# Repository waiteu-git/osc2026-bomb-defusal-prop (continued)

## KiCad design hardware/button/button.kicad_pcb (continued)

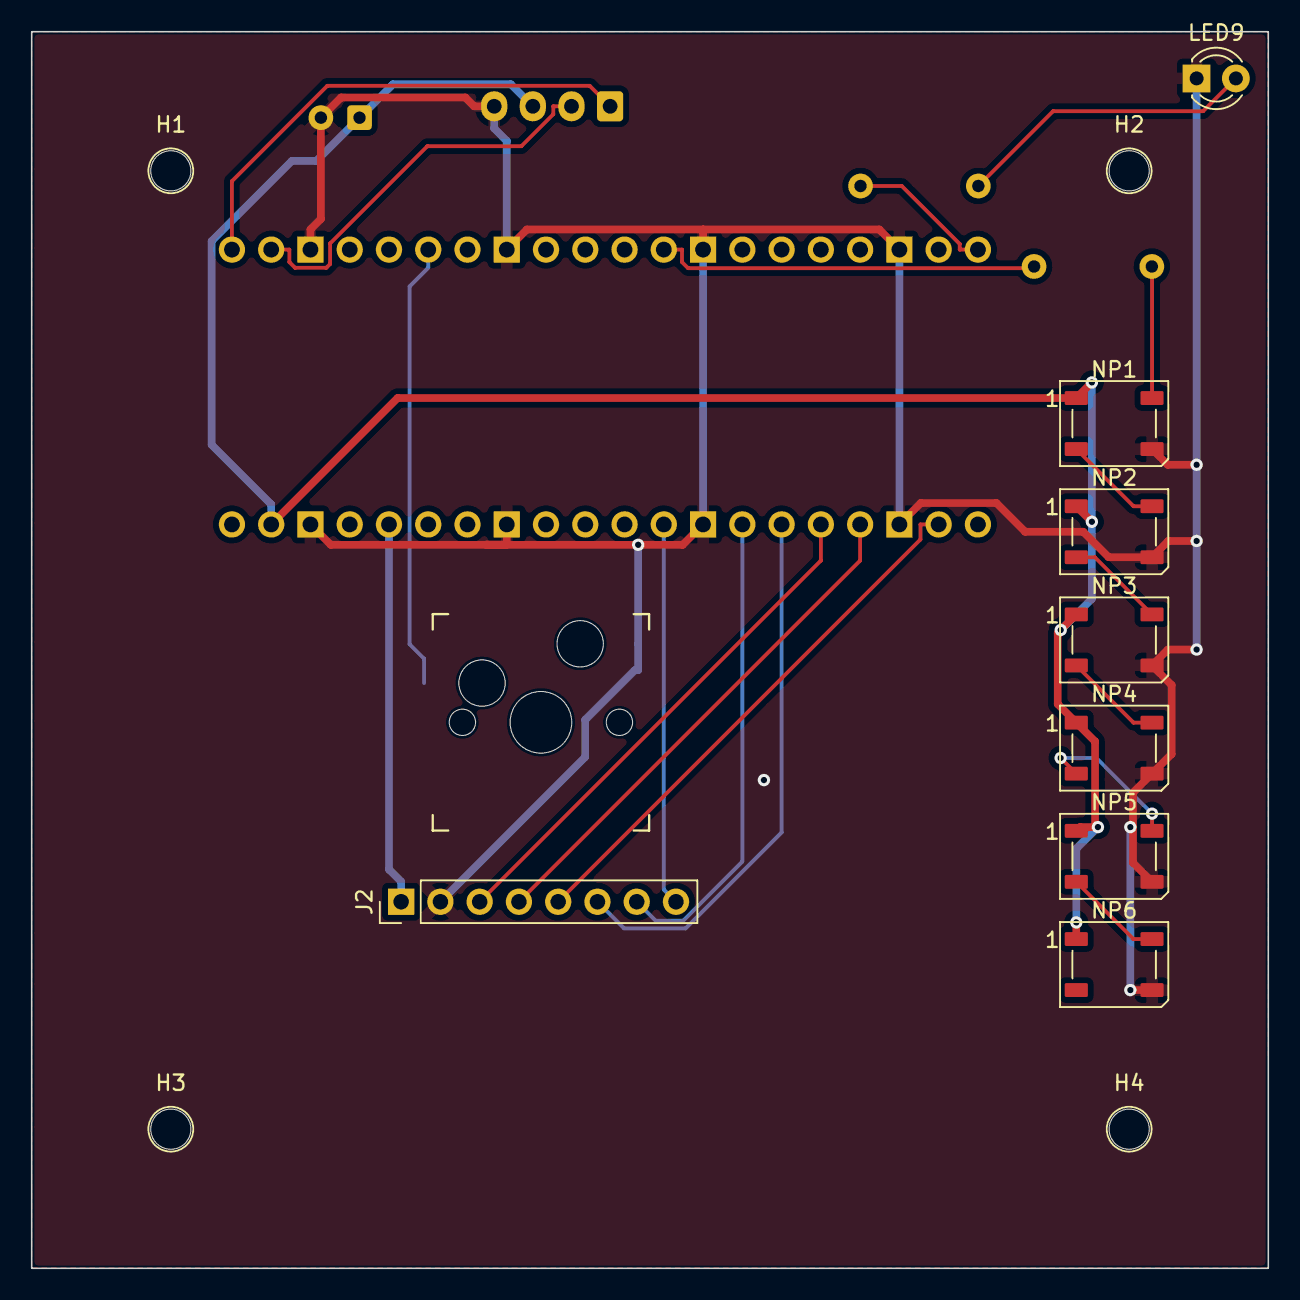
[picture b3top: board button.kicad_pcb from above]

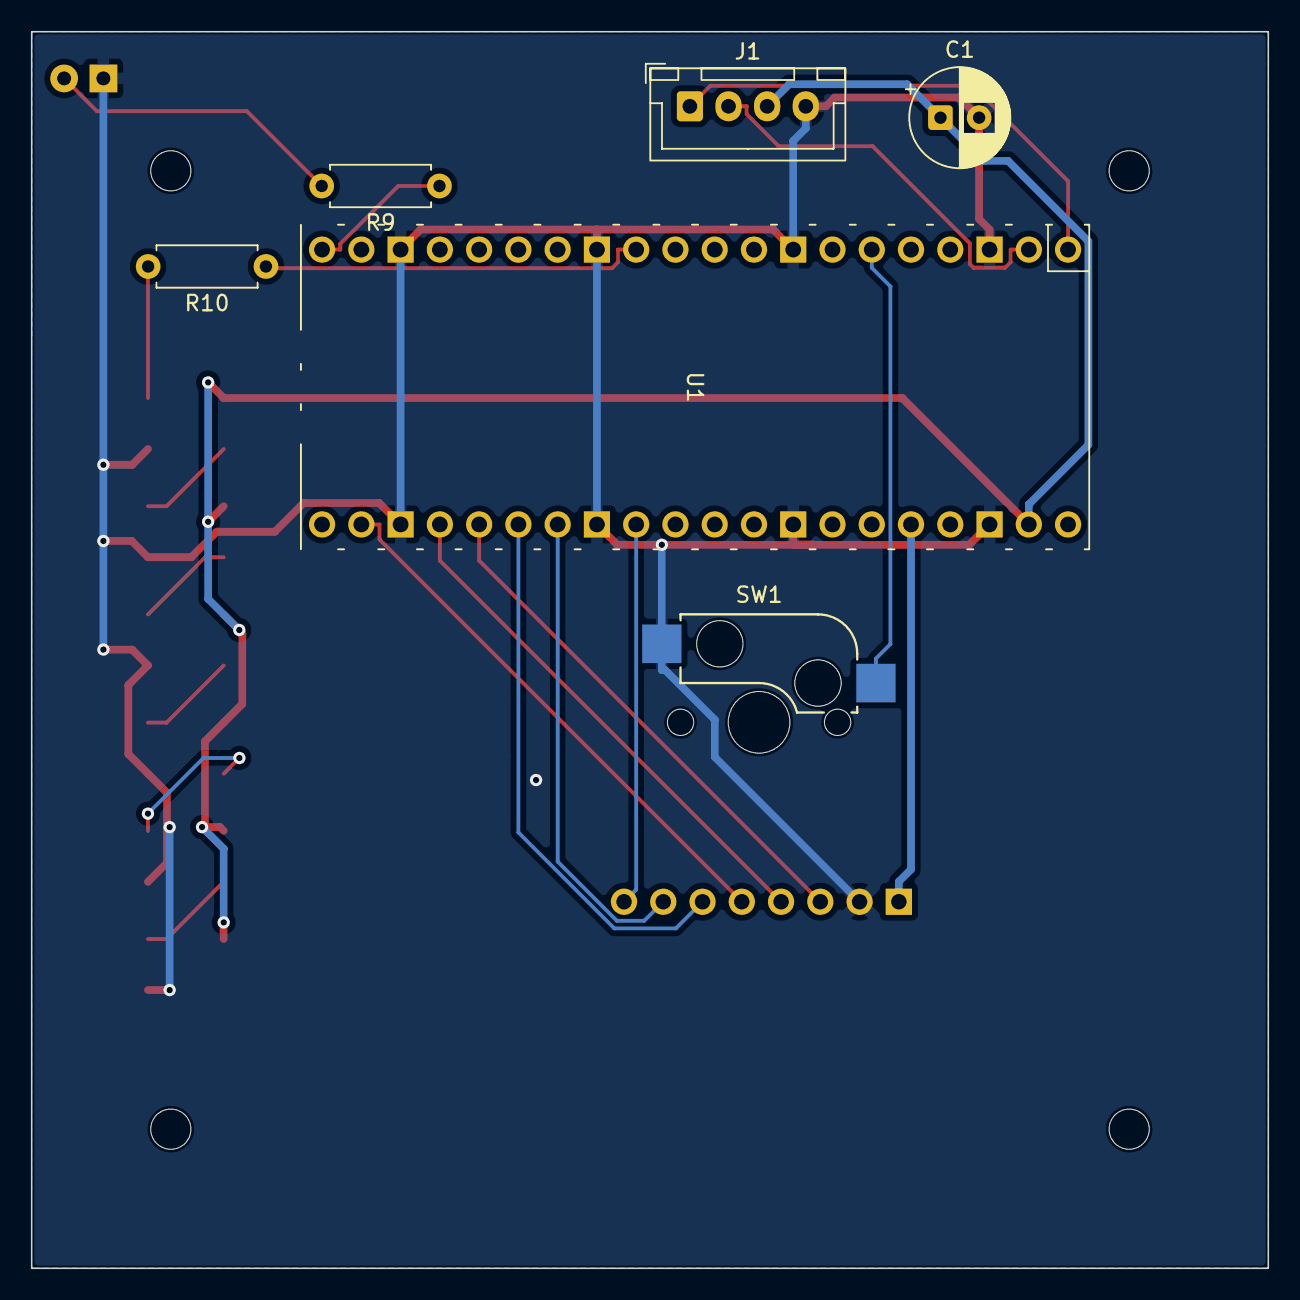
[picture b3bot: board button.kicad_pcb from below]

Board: 2 copper layers, 80.0 x 80.0 mm, 18 parts (5 on the bottom side), 21 nets.

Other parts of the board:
H1, H2, H3, H4: M2.6 hole (dia 2.6mm); MountingHole_2.6mm

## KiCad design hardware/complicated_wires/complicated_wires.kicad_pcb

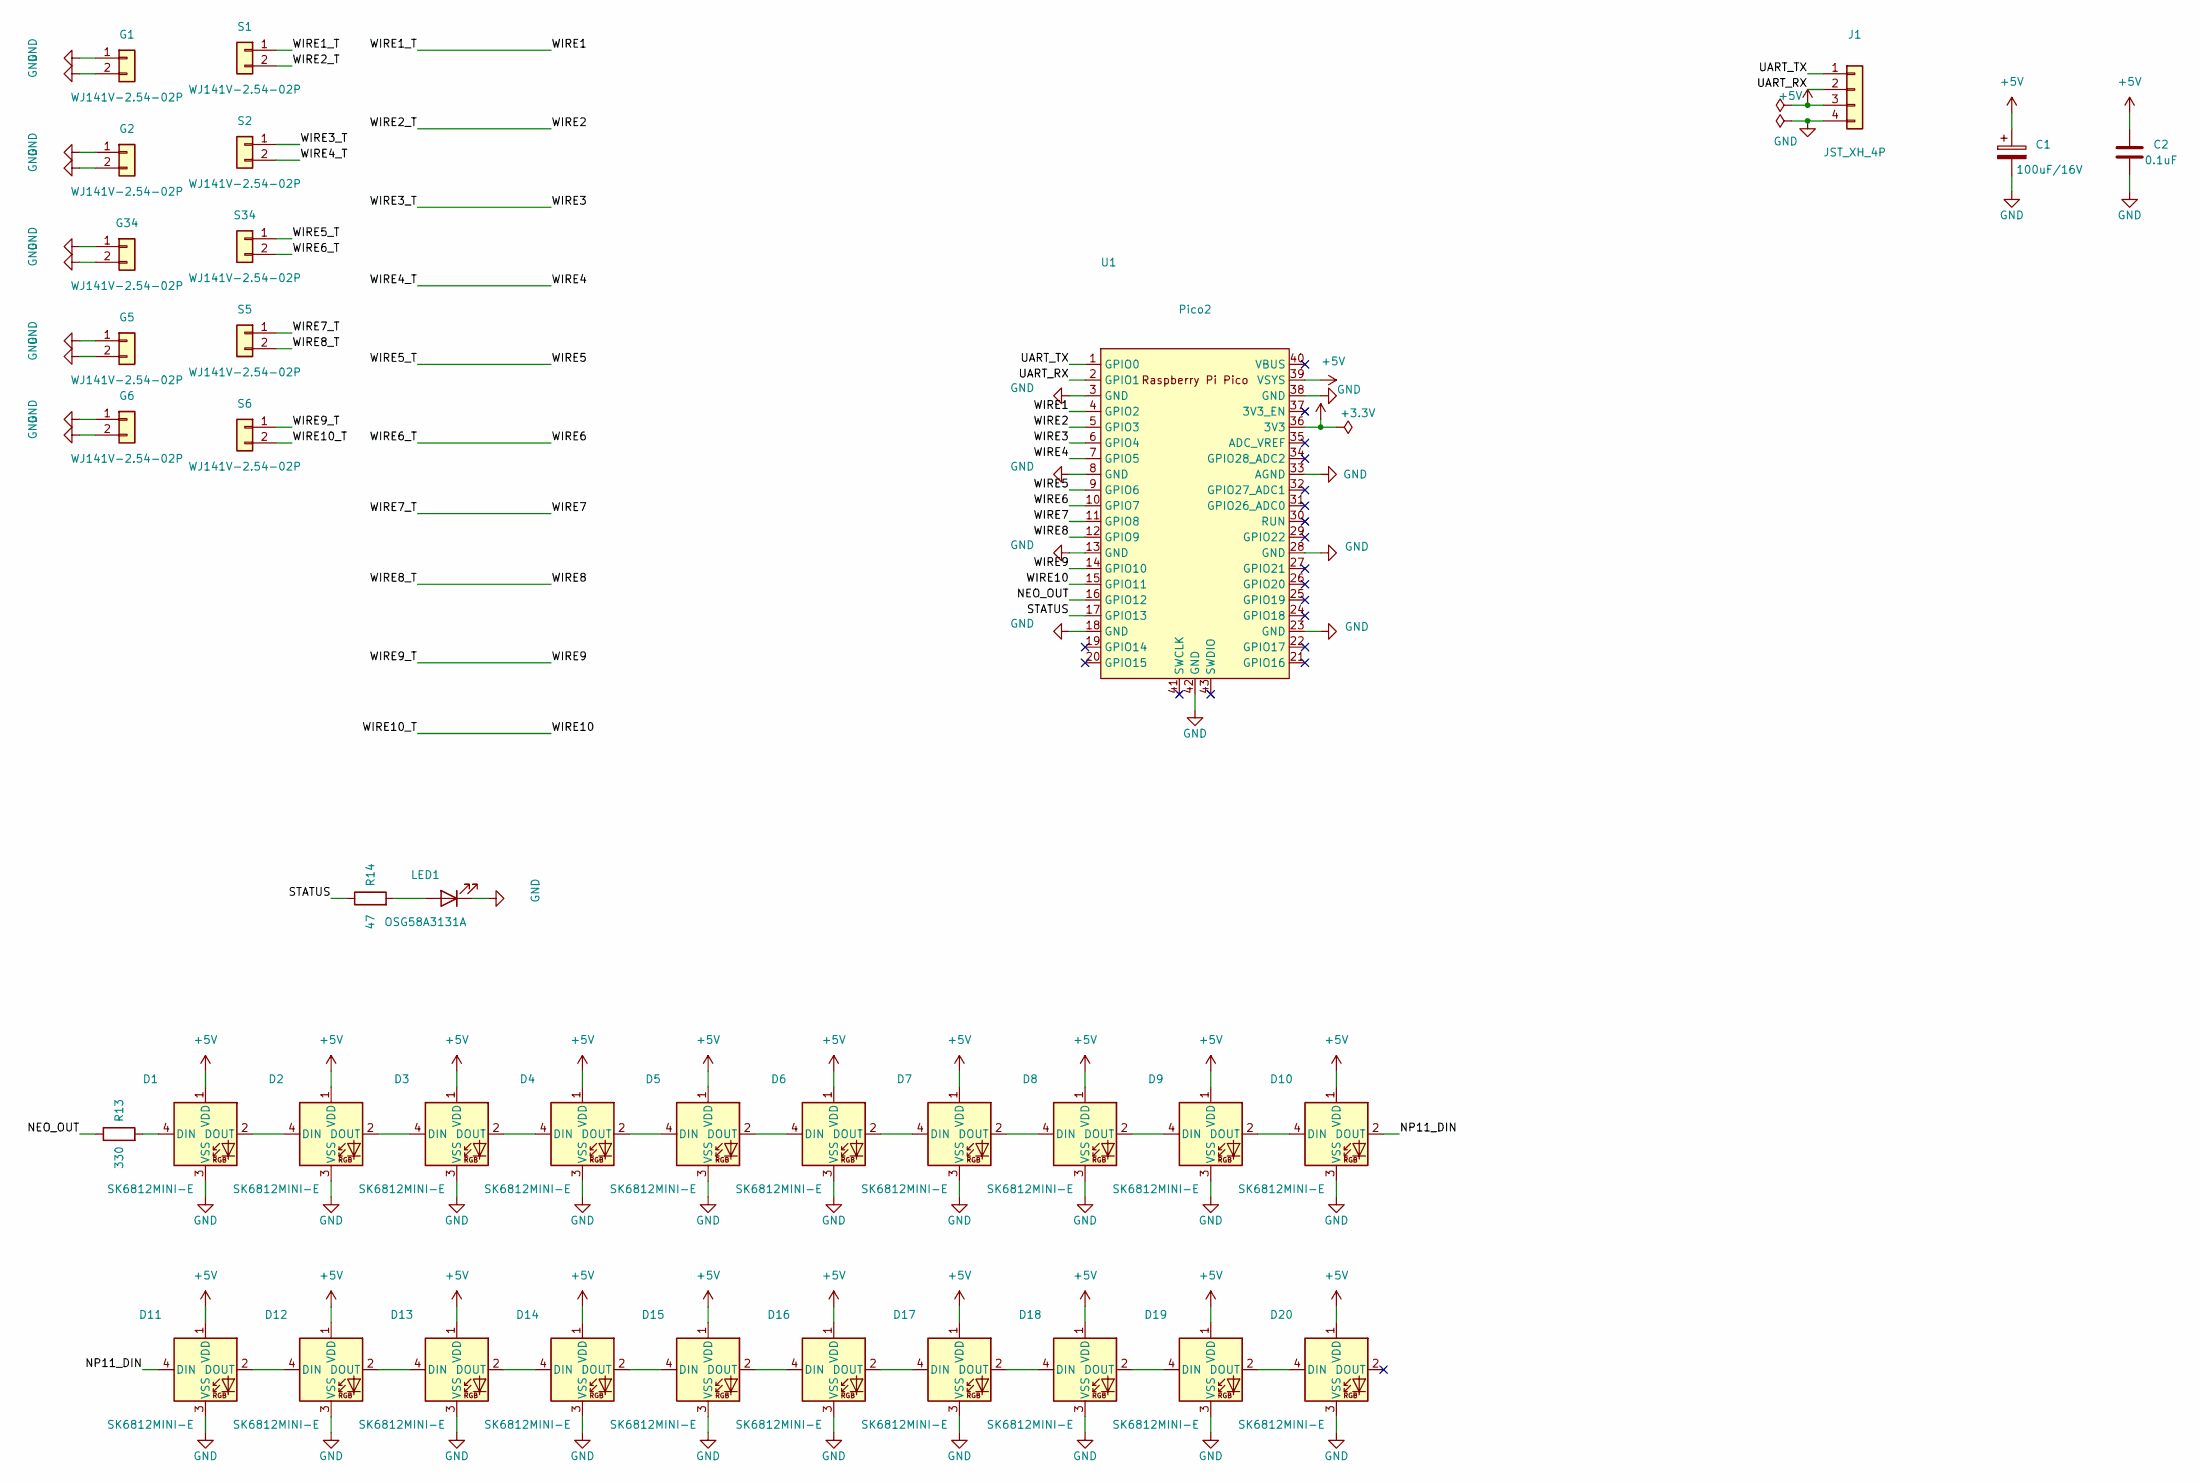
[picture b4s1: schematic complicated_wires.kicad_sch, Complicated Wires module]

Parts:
C1: 100uF/16V; CP_Radial_D6.3mm_P2.50mm
C2: 0.1uF; C_Disc_D5.0mm_W2.5mm_P5.00mm
D1, D2, D3, D4, D5, D6, D7, D8, D9, D10, D11, D12, D13, D14, D15, D16, D17, D18, D19, D20: SK6812MINI-E; LED_SK6812MINI-E_3.2x2.8mm_P1.5mm_ReverseMount
G1, G2, G5, G6, G34: WJ141V-2.54-02P; TerminalBlock_Phoenix_MKDS-1,5-2-5.08_1x02_P5.08mm_Horizont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
J1: JST_XH_4P; JST_XH_B4B-XH-A_1x04_P2.50mm_Vertical
LED1: OSG58A3131A; LED_D5.0mm
R13: 330; R_Axial_DIN0207_L6.3mm_D2.5mm_P10.16mm_Horizontal
R14: 47; R_Axial_DIN0207_L6.3mm_D2.5mm_P10.16mm_Horizontal
S1, S2, S5, S6, S34: WJ141V-2.54-02P; TerminalBlock_Phoenix_MKDS-1,5-2-5.08_1x02_P5.08mm_Horizont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
U1: Pico2; RPi_Pico_SMD_TH

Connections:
+3.3V: U1.36 (3V3)
+5V: C1.1, C2.1, D1.1 (VDD), D2.1 (VDD), D3.1 (VDD), D4.1 (VDD), D5.1 (VDD), D6.1 (VDD), D7.1 (VDD), D8.1 (VDD), D9.1 (VDD), D10.1 (VDD), D11.1 (VDD), D12.1 (VDD), D13.1 (VDD), D14.1 (VDD), D15.1 (VDD), D16.1 (VDD), D17.1 (VDD), D18.1 (VDD), D19.1 (VDD), D20.1 (VDD), J1.3, U1.39 (VSYS)
/NEO_OUT: R13.1, U1.16 (GPIO12)
/NP11_DIN: D10.2 (DOUT), D11.4 (DIN)
/STATUS: R14.1, U1.17 (GPIO13)
/UART_RX: J1.2, U1.2 (GPIO1)
/UART_TX: J1.1, U1.1 (GPIO0)
/WIRE1: S1.1, U1.4 (GPIO2)
/WIRE2: S1.2, U1.5 (GPIO3)
/WIRE3: S2.1, U1.6 (GPIO4)
/WIRE4: S2.2, U1.7 (GPIO5)
/WIRE5: S34.1, U1.9 (GPIO6)
/WIRE6: S34.2, U1.10 (GPIO7)
/WIRE7: S5.1, U1.11 (GPIO8)
/WIRE8: S5.2, U1.12 (GPIO9)
/WIRE9: S6.1, U1.14 (GPIO10)
/WIRE10: S6.2, U1.15 (GPIO11)
GND: C1.2, C2.2, D1.3 (VSS), D2.3 (VSS), D3.3 (VSS), D4.3 (VSS), D5.3 (VSS), D6.3 (VSS), D7.3 (VSS), D8.3 (VSS), D9.3 (VSS), D10.3 (VSS), D11.3 (VSS), D12.3 (VSS), D13.3 (VSS), D14.3 (VSS), D15.3 (VSS), D16.3 (VSS), D17.3 (VSS), D18.3 (VSS), D19.3 (VSS), D20.3 (VSS), G1.1, G1.2, G2.1, G2.2, G5.1, G5.2, G6.1, G6.2, G34.1, G34.2, J1.4, LED1.1 (K), U1.3 (GND), U1.8 (GND), U1.13 (GND), U1.18 (GND), U1.23 (GND), U1.28 (GND), U1.33 (AGND), U1.38 (GND), U1.42 (GND)
unnamed: D1.4 (DIN), R13.2
unnamed: D1.2 (DOUT), D2.4 (DIN)
unnamed: D2.2 (DOUT), D3.4 (DIN)
unnamed: D3.2 (DOUT), D4.4 (DIN)
unnamed: D4.2 (DOUT), D5.4 (DIN)
unnamed: D5.2 (DOUT), D6.4 (DIN)
unnamed: D6.2 (DOUT), D7.4 (DIN)
unnamed: D7.2 (DOUT), D8.4 (DIN)
unnamed: D8.2 (DOUT), D9.4 (DIN)
unnamed: D9.2 (DOUT), D10.4 (DIN)
unnamed: D11.2 (DOUT), D12.4 (DIN)
unnamed: D12.2 (DOUT), D13.4 (DIN)
unnamed: D13.2 (DOUT), D14.4 (DIN)
unnamed: D14.2 (DOUT), D15.4 (DIN)
unnamed: D15.2 (DOUT), D16.4 (DIN)
unnamed: D16.2 (DOUT), D17.4 (DIN)
unnamed: D17.2 (DOUT), D18.4 (DIN)
unnamed: D18.2 (DOUT), D19.4 (DIN)
unnamed: D19.2 (DOUT), D20.4 (DIN)
unnamed: LED1.2 (A), R14.2

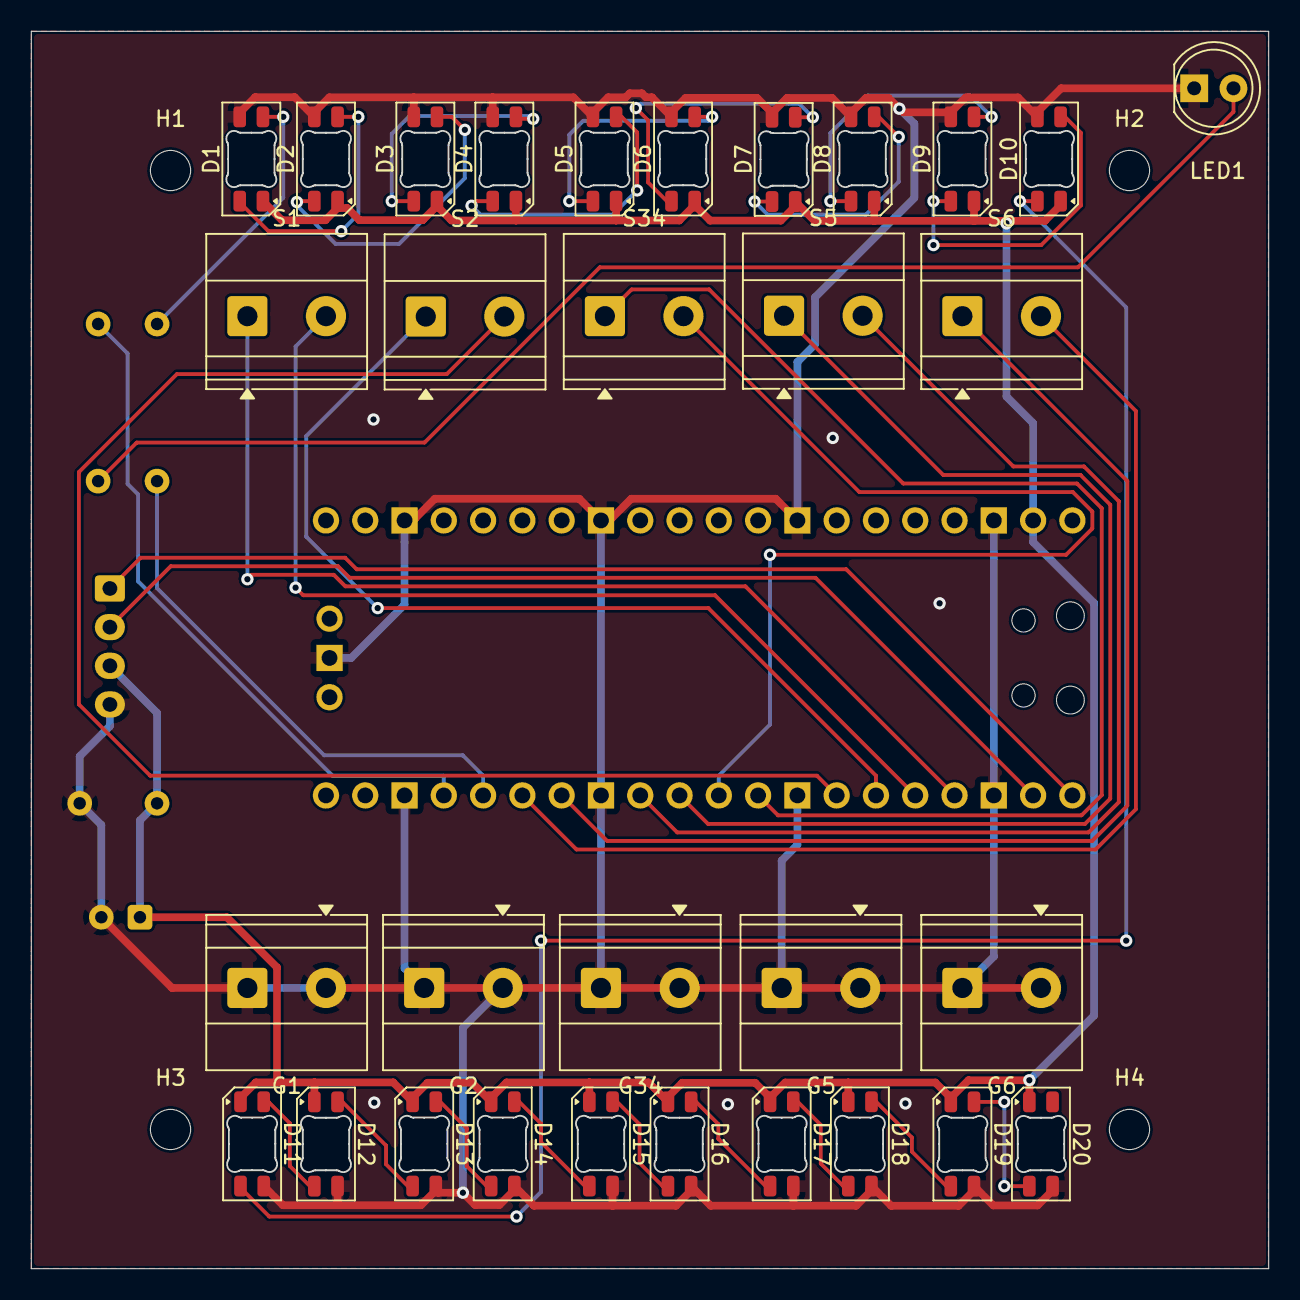
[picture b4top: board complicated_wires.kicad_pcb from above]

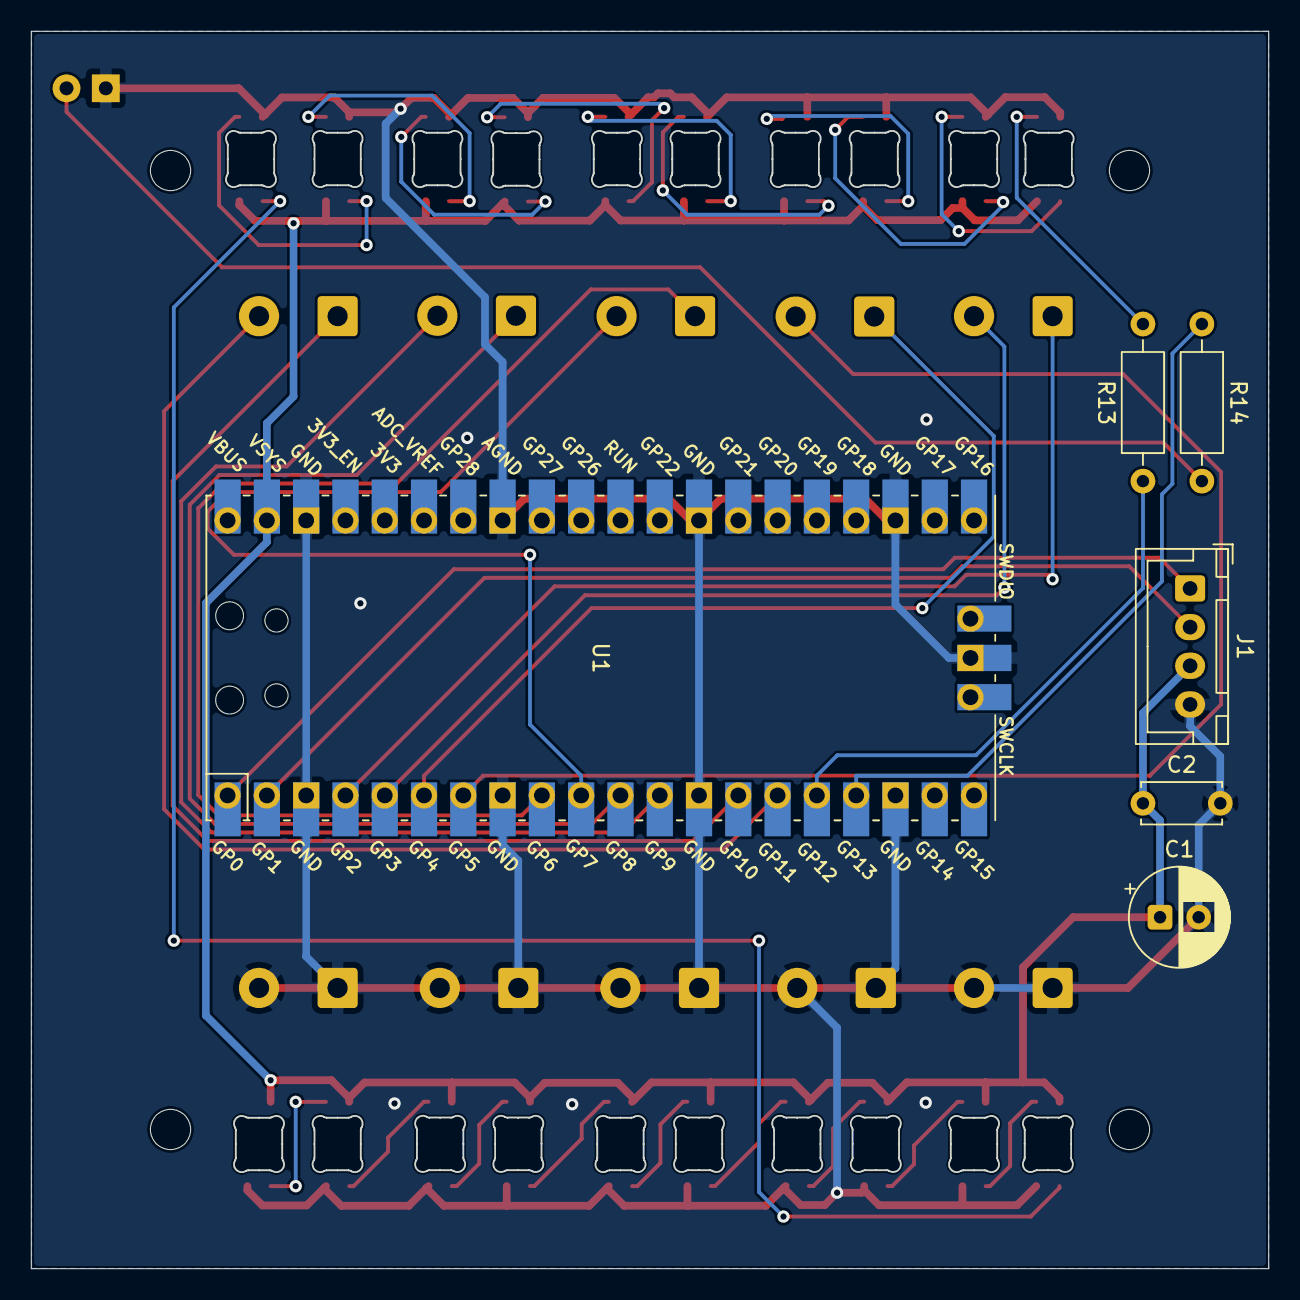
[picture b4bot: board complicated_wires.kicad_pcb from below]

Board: 2 copper layers, 80.0 x 80.0 mm, 41 parts (6 on the bottom side), 37 nets.

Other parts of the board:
H1, H2, H3, H4: MountingHole_2.6mm

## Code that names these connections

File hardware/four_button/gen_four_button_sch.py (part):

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    37: (17.78, 16.51),   38: (17.78, 19.05),  39: (17.78, 21.59),  40: (17.78, 24.13),
}
PICO_NAMES = {
    1: "GPIO0", 2: "GPIO1", 3: "GND", 4: "GPIO2", 5: "GPIO3", 6: "GPIO4", 7: "GPIO5", 8: "GND",
    9: "GPIO6", 10: "GPIO7", 11: "GPIO8", 12: "GPIO9", 13: "GND", 14: "GPIO10", 15: "GPIO11",
    16: "GPIO12", 17: "GPIO13", 18: "GND", 19: "GPIO14", 20: "GPIO15", 21: "GPIO16", 22: "GPIO17",
    23: "GND", 24: "GPIO18", 25: "GPIO19", 26: "GPIO20", 27: "GPIO21", 28: "GND", 29: "GPIO22",
    30: "RUN", 31: "GPIO26_ADC0", 32: "GPIO27_ADC1", 33: "AGND", 34: "GPIO28_ADC2",
    35: "ADC_VREF", 36: "3V3", 37: "3V3_EN", 38: "GND", 39: "VSYS", 40: "VBUS",
}
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# 各SK6812のVDD/VSSにはデコップリングコンデンサ(0.1uF)を1個ずつ並列配置。
r10_pin1 = abs_pt(R10_POS[:2], R_PINS[1])
r10_pin2 = abs_pt(R10_POS[:2], R_PINS[2])
stub(r10_pin1, (r10_pin1[0], round(r10_pin1[1] - G(4), 4)), "NEOPIXEL_DATA", 0)
component_pins += [("R10.1", r10_pin1), ("R10.2", r10_pin2)]

chain_refs = list(DIAMOND_SW.items())
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# --- 状態LED(緑) -----------------------------------------------------------
rstatus_pin1 = abs_pt(STATUS_R_POS[:2], R_PINS[1])
rstatus_pin2 = abs_pt(STATUS_R_POS[:2], R_PINS[2])
stub(rstatus_pin1, (rstatus_pin1[0], round(rstatus_pin1[1] - G(4), 4)), "STATUS_LED", 0)
led_status_anode = abs_pt(STATUS_LED_POS[:2], LED_PINS[2])
led_status_cathode = abs_pt(STATUS_LED_POS[:2], LED_PINS[1])
wire(rstatus_pin2, led_status_anode, "STATUS_LED_ANODE")
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# --- モード選択スイッチ(GP11、内部プルアップ、GNDで「ひし形モード」) --------
mode_pin2 = abs_pt(MODE_SW_POS[:2], SW_PINS[2])
mode_pin1 = abs_pt(MODE_SW_POS[:2], SW_PINS[1])
stub(mode_pin2, (round(mode_pin2[0] + G(4), 4), mode_pin2[1]), "MODE_SEL", 0)

# ===========================================================================
# 部品配置
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
lines.append(placed_symbol("Connector_Generic:Conn_01x04", "J1", "MODULE_JST_XH_4P",
                            "Connector_JST:JST_XH_B4B-XH-A_1x04_P2.50mm_Vertical", J1_POS, [1, 2, 3, 4],
                            "Host connector, JST XH 4-pole. Pin1=GPIO0(UART0 TX, module->host), "
                            "Pin2=GPIO1(UART0 RX, host->module), Pin3=VCC(5V, from host per-slot polyfuse "
                            "MF-RX030/72-0 0.3A hold), Pin4=GND. Common to all puzzle modules (see ハブ連絡事項.md).",
                            ref_at=(J1_POS[0], J1_POS[1] - 8.89, 0), val_at=(J1_POS[0], J1_POS[1] - 6.35, 0)))

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
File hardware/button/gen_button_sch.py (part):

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    41: (-2.54, -29.21),  42: (0.0, -29.21),   43: (2.54, -29.21),
}
PICO_NAMES = {
    1: "GPIO0", 2: "GPIO1", 3: "GND", 4: "GPIO2", 5: "GPIO3", 6: "GPIO4", 7: "GPIO5", 8: "GND",
    9: "GPIO6", 10: "GPIO7", 11: "GPIO8", 12: "GPIO9", 13: "GND", 14: "GPIO10", 15: "GPIO11",
    16: "GPIO12", 17: "GPIO13", 18: "GND", 19: "GPIO14", 20: "GPIO15", 21: "GPIO16", 22: "GPIO17",
    23: "GND", 24: "GPIO18", 25: "GPIO19", 26: "GPIO20", 27: "GPIO21", 28: "GND", 29: "GPIO22",
    30: "RUN", 31: "GPIO26_ADC0", 32: "GPIO27_ADC1", 33: "AGND", 34: "GPIO28_ADC2",
    35: "ADC_VREF", 36: "3V3", 37: "3V3_EN", 38: "GND", 39: "VSYS", 40: "VBUS",
    41: "SWCLK", 42: "GND", 43: "SWDIO",
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    8: (29, "GP22", "LCD_BL"),
}

# --- ボタン押下スイッチ(SW1、GP4に並列。各スイッチのpin2から同名ラベル"BTN"で結ぶ) ----
SW_REFS = ["SW1"]
sw_defs = {ref: dict(place=(SW_X, round(SW_Y0 + G(10) * i, 4), 0)) for i, ref in enumerate(SW_REFS)}

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        rled_place=rled_place, rled_pin1=rled_pin1, rled_pin2=rled_pin2,
    )

# --- 状態LED(緑、GP15): R9のpin1から上へ枝を出し、ラベルSTATUS_LEDでPicoへ結ぶ ---------
STATUS_R_Y1 = G(80)
RSTATUS_POS = (STATUS_R_X, round(STATUS_R_Y1 + R_PINS[1][1], 4), 0)
rstatus_pin1 = abs_pt(RSTATUS_POS[:2], R_PINS[1])
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    p_j2 = abs_pt(J2_POS[:2], J2_PINS8[pin_j])
    stub(p_j2, (round(p_j2[0] - STUB, 4), p_j2[1]), net, 180)

# --- ボタン押下スイッチ(SW1): pin2から右へ短い枝を出し、ラベルBTNで結ぶ --------------------
sw_pin2 = {ref: abs_pt(sw_defs[ref]["place"][:2], SW_PUSH_PINS[2]) for ref in SW_REFS}
for ref in SW_REFS:
    p = sw_pin2[ref]
    stub(p, (round(p[0] + G(4), 4), p[1]), "BTN", 0)

# --- ストリップLED 4色チャンネル -------------------------------------------------
stub(r10_pin1, r10_label_pt, "NEO_DIN", 0)
wire(r10_pin2, abs_pt(NP_POS["NP1"][:2], NP_PINS[4]), "NEO_DIN_R")
for i in range(len(NP_REFS) - 1):
    wire(abs_pt(NP_POS[NP_REFS[i]][:2], NP_PINS[2]), abs_pt(NP_POS[NP_REFS[i + 1]][:2], NP_PINS[4]), f"NEO_CHAIN{i + 1}")
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    wire(g["led_a"], g["rled_pin1"], f"ANODE{k+1}")

# --- 状態LED(緑) -------------------------------------------------------------
stub(rstatus_pin1, rstatus_label_pt, "STATUS_LED", 0)
wire(rstatus_pin2, led_status_anode, "STATUS_LED_ANODE")

# --- 部品配置: Pico -----------------------------------------------------------
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# --- J1(UART) -----------------------------------------------------------------
lines.append(placed_symbol("Connector_Generic:Conn_01x04", "J1", "MODULE_JST_XH_4P",
                            "Connector_JST:JST_XH_B4B-XH-A_1x04_P2.50mm_Vertical", J1_POS, [1, 2, 3, 4],
                            "Host connector, JST XH 4-pole. Pin1=GPIO0(UART0 TX, module->host), "
                            "Pin2=GPIO1(UART0 RX, host->module), Pin3=VCC(5V, from host per-slot polyfuse "
                            "MF-RX030/72-0 0.3A hold), Pin4=GND. Common to all puzzle modules (see ハブ連絡事項.md).",
                            ref_at=(J1_POS[0], J1_POS[1] - 8.89, 0), val_at=(J1_POS[0], J1_POS[1] - 6.35, 0)))

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    lines.append(placed_symbol("Switch:SW_Push", ref, "SW_Push", "Button_Local:Kailh_socket_MX",
                                place, [1, 2],
                                f"Button press detection, one Kailh MX hot-swap socket under the keytop (2026-10-01; same switch/socket as the four_button module; MX-compatible switch plugs in; replaces the 12mm tact). "
                                f"Wired onto GP4. Pico physical pin 6 (GPIO4), "
                                f"internal pull-up, no external resistor. Pin1=GND side, Pin2=GPIO side.",
                                ref_at=(round(SW_X, 4), round(place[1] - 5.08, 4), 0), hide_value=True))

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
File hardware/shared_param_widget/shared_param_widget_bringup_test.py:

# Shared parameter widget - hardware bring-up test (MicroPython, Raspberry Pi Pico 2 / Pico 2 W)
# 目的: 配線確認のみ。本番のファームウェア(共有情報バイトの生成・OLED描画内容)はソフト担当が別途実装する。
#
# 注意: このウィジェットは他モジュール(キーパッド等)と違い、専用マイコン・専用I2Cアドレスを
#       持たない。ホストのPico 2 WのGPIOに直接配線される設計なので、このテストは
#       「ホストと同じGPIO配置(GP2-7, I2C0=GP0/GP1)を持つPico」で実行する想定。
#       本番のホスト基板そのものでも、配線検証用の予備Picoでもどちらでもよい。
#
# 配線(host_design_notes.md J7/J8で確定済み):
#   GPIO2 (SHARED_ODDEVEN) : スライドスイッチ(SS-12D00G3) - シリアル末尾奇偶
#   GPIO3 (SHARED_VOWEL)   : スライドスイッチ - シリアル母音有無
#   GPIO4 (SHARED_BATT2)   : スライドスイッチ - バッテリー2本以上
#   GPIO5 (SHARED_BATT3)   : スライドスイッチ - バッテリー3本以上(優先度低)
#   GPIO6 (SHARED_PORT)    : スライドスイッチ - パラレルポート有無
#     -> 上記5個はいずれも内部プルアップ使用。スイッチのもう片方はGND直結、外付け抵抗なし。
#        Low(0) = 有効(スイッチが倒れている/該当する側)。
#   GPIO7 (SHARED_LED)     : 白色LED(OSW54K3131A) + 電流制限抵抗(100〜150Ω、実測して調整)
#     -> 本番ではホストが能動的にHigh/Lowを切り替える(インジケーター表示の点灯/消灯)。
#   GPIO0/1 (I2C0 SDA/SCL) : 既存の6モジュール共有I2Cバスに相乗り。OLED(SSD1315, 0.96インチ)、
#     アドレス0x3C(SA0がモジュール基板側でGNDに繋がっている前提、現物到着後に要確認)。
#     プルアップ抵抗はホスト側の分配ポイントに既設のものを流用(このウィジェット側には付けない)。
#
# 準備:
#   1. MicroPython公式の定番ssd1306ドライバ(ssd1306.py)を、このファイルと同じ場所に
#      一緒にアップロードしておくこと(host_i2c_oled_test.pyと同じもの)
#   2. 上記の配線を行う
#
# 使い方: Thonny等でPicoに書き込んで実行。
#   1. 起動時にLEDが3回点滅すればLED回路はOK
#   2. i2c.scan()の結果に0x3Cが出て、OLEDに"I2C OK!"が表示されればOLED回路もOK
#   3. スイッチを1個ずつ倒して、対応するラベル(SHARED_ODDEVEN等)がREPLに表示され、
#      倒している間だけLEDが点灯すれば配線OK
#      (このLED連動はブリングアップテスト専用の簡易確認用。本番ではLEDはスイッチと無関係に
#       ホストが独立して点灯/消灯を制御する)

from machine import Pin, I2C
import time

try:
    import ssd1306
except ImportError:
    print("ssd1306.py が見つかりません。事前にPicoへアップロードしてください。")
    raise

SWITCH_PINS = {
    "SHARED_ODDEVEN": 2,
    "SHARED_VOWEL": 3,
    "SHARED_BATT2": 4,
    "SHARED_BATT3": 5,
    "SHARED_PORT": 6,
}
switches = {name: Pin(gp, Pin.IN, Pin.PULL_UP) for name, gp in SWITCH_PINS.items()}
led = Pin(7, Pin.OUT)

I2C_ID = 0
SDA_PIN = 0
SCL_PIN = 1
FREQ = 400000
OLED_ADDR = 0x3C


def blink(n, interval=0.15):
    for _ in range(n):
        led.value(1)
        time.sleep(interval)
        led.value(0)
        time.sleep(interval)


print("=== Shared parameter widget bring-up test start ===")
blink(3)  # LED回路の生存確認

i2c = I2C(I2C_ID, sda=Pin(SDA_PIN), scl=Pin(SCL_PIN), freq=FREQ)
addrs = i2c.scan()
print("Found I2C devices:", ["0x{:02X}".format(a) for a in addrs])

if OLED_ADDR not in addrs:
    print("OLED(0x3C)が見つかりません。配線・SA0の設定を確認してください。")
else:
    oled = ssd1306.SSD1306_I2C(128, 64, i2c)
    oled.fill(0)
    oled.text("I2C OK!", 0, 0)
    oled.text("SharedParamWidget", 0, 16)
    oled.show()
    print("OLEDに表示しました。画面に「I2C OK!」が見えればOLED回路は正常です。")

prev_state = {name: 1 for name in SWITCH_PINS}  # プルアップなので未操作=1

while True:
    any_active = False
    for name, gp in SWITCH_PINS.items():
        val = switches[name].value()
        if val == 0:
            any_active = True
            if prev_state[name] == 1:
                print("{} (GPIO{}) active".format(name, gp))
        else:
            if prev_state[name] == 0:
                print("{} (GPIO{}) inactive".format(name, gp))
        prev_state[name] = val
    led.value(1 if any_active else 0)
    time.sleep(0.02)
